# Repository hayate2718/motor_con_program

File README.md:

# モータドライバ実験用コントローラ
<b> pic16f1827用</b><br>
1. pwm周波数はpwm_freqに入れて設定してください

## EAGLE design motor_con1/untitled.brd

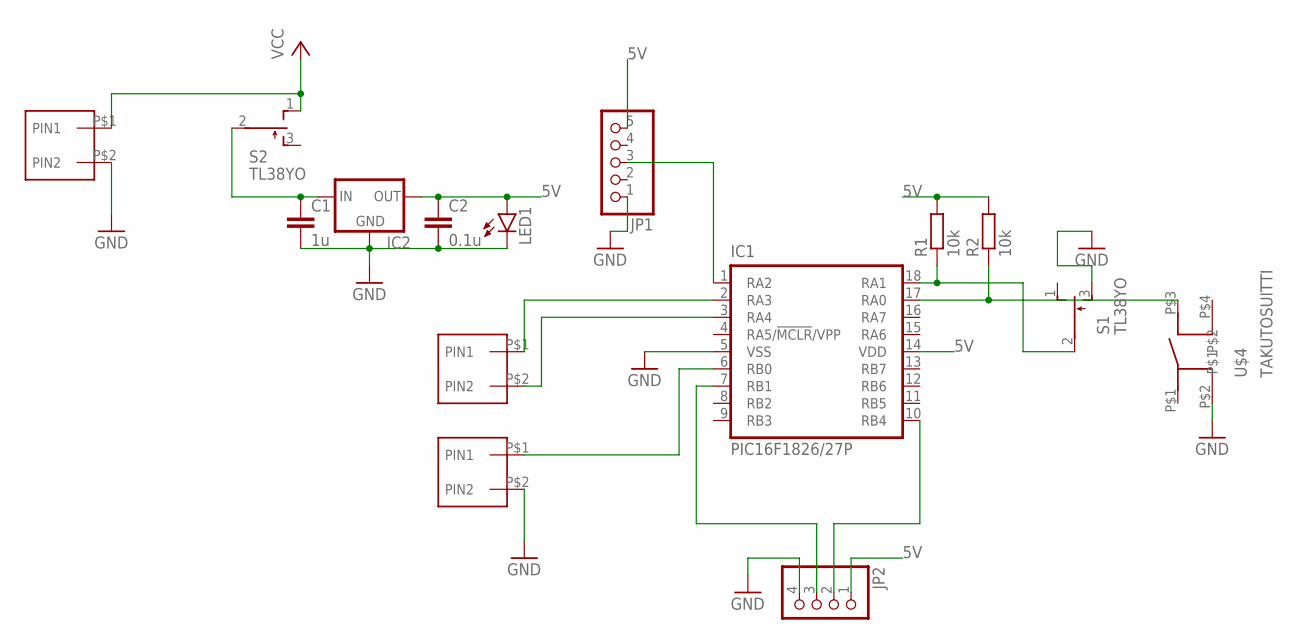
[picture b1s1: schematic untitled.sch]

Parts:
C1: 1u; C025-025X050
C2: 0.1u; C025-025X050
IC1: PIC16F1826/27P; DIL18
IC2: 78XXS
JP1: PINHD-1X5; 1X05
JP2: PINHD-1X4; 1X04
LED1: LED5MM
R1, R2: 10k; 0207/10
S1, S2: TL38YO; TL3XYO
U$1, U$2, U$3: TERMINAL_2
U$4: TAKUTOSUITTI

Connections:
5V: C2.1, IC1.14 (VDD), IC2.OUT, JP1.5, JP2.1, LED1.A, R1.2, R2.2
GND: C1.2, C2.2, IC1.5 (VSS), IC2.GND, JP1.1, JP2.4, LED1.K (C), S1.3 (S), U$1.P$2 (PIN2), U$3.P$2 (PIN2), U$4.P$2
unnamed: IC1.1 (RA2), JP1.3
unnamed: IC1.18 (RA1), R1.1, S1.2
unnamed: C1.1, IC2.IN, S2.2
unnamed: IC1.10 (RB4), JP2.2
unnamed: IC1.7 (RB1), JP2.3
unnamed: IC1.2 (RA3), U$2.P$1 (PIN1)
unnamed: IC1.3 (RA4), U$2.P$2 (PIN2)
unnamed: IC1.6 (RB0), U$3.P$1 (PIN1)
unnamed: IC1.17 (RA0), R2.1, U$4.P$3 (S)
VCC: S2.1 (O), U$1.P$1 (PIN1)

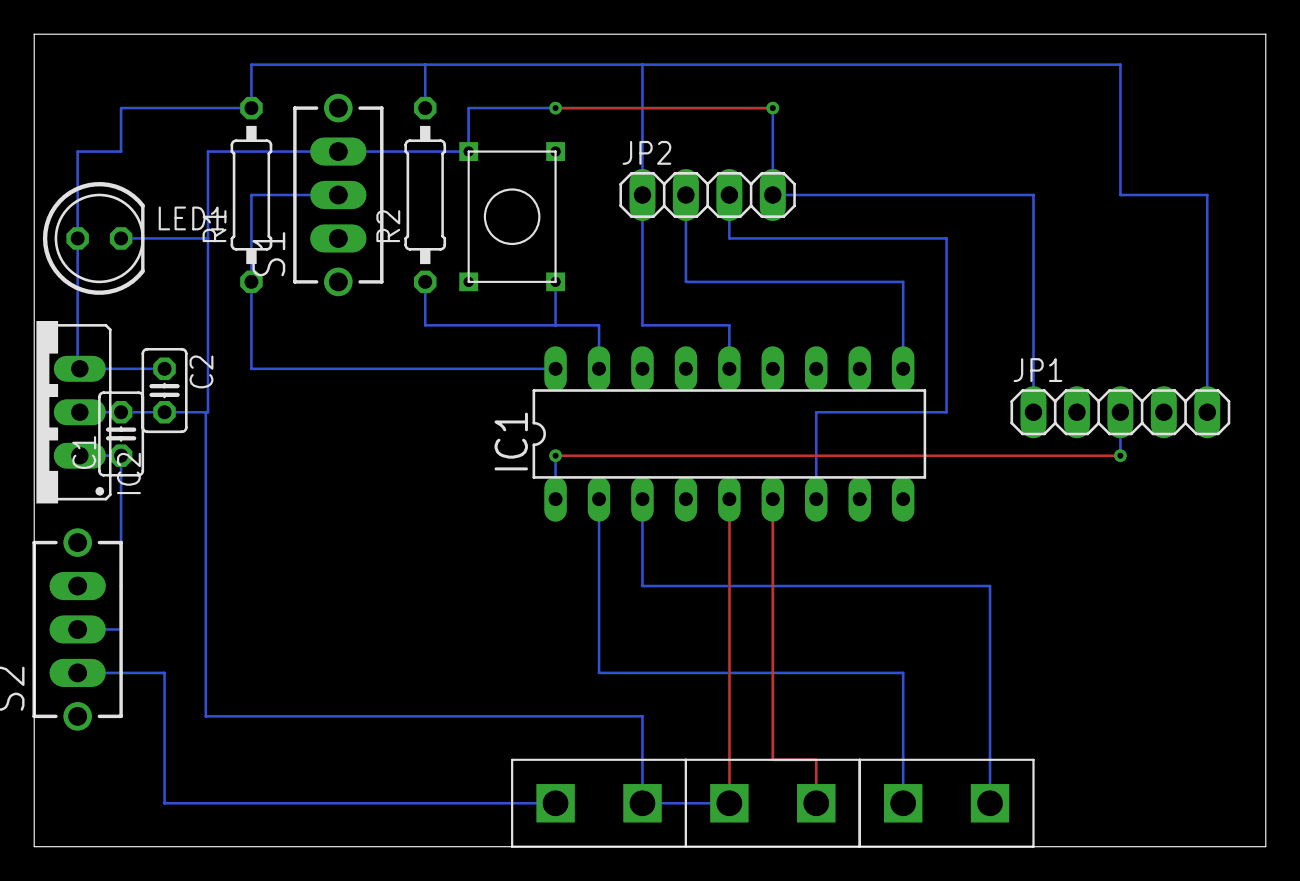
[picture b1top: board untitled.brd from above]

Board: 2 copper layers, 72.0 x 47.5 mm, 15 parts (0 on the bottom side), 12 nets.

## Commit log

2020-09-23 picマイコンのモータ制御用プログラム
    pic16f1827用
2020-11-24 バグ直した
    小数点以下の計算をしなくていいようにしたことで表示が100％を超えなくなった
